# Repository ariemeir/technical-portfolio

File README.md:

# Technical Portfolio — Arie Meir

Representative projects, published for reference.

**→ [Browse all source on GitHub](https://github.com/ariemeir/technical-portfolio)**

## Projects

### [RoboImplant](roboimplant/) — non-invasive spinal implant adjustment system

A motorized orthopedic implant that lengthens a spinal distraction rod without
surgery, for treating early-onset scoliosis in growing children. Full-stack
across four disciplines:

- **Embedded** — AVR C firmware on an ATmega1284P: real-time motor control via a
  DS1267 digital pot into a maxon ESCON servo controller, interrupt-driven
  rotation counting, and current-threshold coupling detection as the primary
  safety interlock.
- **Mobile** — Android clinician console over Bluetooth SPP, with a custom
  line-oriented ASCII protocol, live telemetry, 3D visualization, and patient
  records.
- **Electronics** — EAGLE schematic and board layout for the controller,
  including the analog current/voltage sensing chain.
- **Mechanical** — SolidWorks enclosure for the handheld driver unit.

<p align="center">
  
  <br>
  <em>The handheld driver unit (v1)</em>
</p>

**→ [Read the one-page case study (PDF)](roboimplant/docs/roboimplant-case-study-arie-meir.pdf)**

Research prototype, ~2012–2013. Not a cleared medical device.
See [`roboimplant/NOTICE.md`](roboimplant/NOTICE.md) for rights and third-party
attribution.

---

### [3D Scanner](3dscanner/) — turntable photogrammetry rig

A DIY tabletop 3D scanner built to solve a real fabrication problem: an artist needed
larger and deeper variants of a commercially molded clay flower that existed only as a
physical object. It takes that object and produces a printable, watertight STL. Five
subsystems bound together by explicit contracts:

- **iOS** — **ScannerCam**, an iPhone camera server with a hand-rolled HTTP/1.1
  stack on `NWListener`: 13 REST routes, bearer auth with constant-time comparison,
  Keychain token storage, and hard locks on focus, exposure, and white balance.
  SwiftUI + AVFoundation, zero third-party packages.
- **Orchestration** — a Python session controller driving the scan loop across two
  machines, with idempotent retries, resumable sessions, and a five-stage SHA-256
  integrity chain from the phone's memory to the final archive.
- **Embedded** — an Arduino that controls the turntable by *impersonating its
  infrared remote*, replaying NEC codes reverse-engineered with a majority-vote
  capture sketch. No data port, no feedback, no encoder.
- **Reconstruction** — a Swift CLI over Apple Object Capture (RealityKit), chosen
  after COLMAP was tested and rejected for being CUDA-only on Apple Silicon.
- **Print prep** — a PyMeshLab pass that makes the mesh watertight, orients it by
  PCA, and scales it to real millimetres for printing and silicone-mold casting.

<p align="center">
  
  <br>
  <em>Input and output: the original ceramic dish, and a printed reproduction
  scanned from it.</em>
</p>

```
object ─→ 72 photos ─→ pose solve ─→ textured mesh ─→ watertight STL ─→ printed master
          locked        Object          USDZ/OBJ        PyMeshLab         silicone mold
          optics        Capture                         repair            → cast copies
```

The engineering centrepiece is control of an actuator that cannot be observed: the
turntable answers only to a fire-and-forget infrared *toggle*, so the controller
tracks an explicit assumed state and halts for human realignment on any ambiguity
rather than guessing and silently desynchronising the scan.

**→ [Read the one-page case study (PDF)](3dscanner/docs/3dscanner-case-study-arie-meir.pdf)**
· [Engineering log](3dscanner/docs/engineering-log.md)
· [Technical spec](3dscanner/docs/scannercam_spec.md)

Personal project, 2026. Working single-operator rig at late-prototype maturity.
See [`3dscanner/NOTICE.md`](3dscanner/NOTICE.md) for rights and attribution.

---

### [WifeSignal](wifesignal/) — a traffic light for the office door

A three-colour desk lamp that lets one person in the house tell another *how much
this can wait*. The office is a separate building: music on, windows closed, phone
face-down and unchecked for hours — which is the point, and which makes it a sealed
box. Text-and-hope fails when it matters; walking over always costs an interruption
whether or not the thing was urgent. The missing piece was never notification, it
was **priority expressed before the interruption happens**. Five components across
four disciplines:

- **iOS** — a SwiftUI app in 333 lines with no third-party packages and no
  Bluetooth: three priority buttons, a 5 s status poll, and a *Waiting… → Seen ♥*
  acknowledgement card that closes the loop for the sender.
- **Server** — a 290-line aiohttp + bleak bridge on a Mac, sharing one asyncio event
  loop, that exists because an iPhone cannot reliably be a BLE central for a device
  in another building. Bearer auth with constant-time comparison, exposed to a
  Tailscale tailnet only.
- **Embedded** — ESP32-C3 firmware over NimBLE exposing one service, one
  characteristic, one byte, with physical button presses as the acknowledgement path.
- **Electronics** — a custom two-layer KiCad board: three low-side lamp drivers,
  entirely through-hole, shaped and notched to match the enclosure.
- **Mechanical** — a 440-line Fusion 360 *script* that generates the two-part
  enclosure from derived dimensions, versioned in-band and guarded step by step.

<p align="center">
  
  <br>
  <em>Green — <strong>whenever you're free</strong>. The speaker beside it is the
  reason the project exists.</em>
</p>

```
tap ─→ HTTPS ─→ aiohttp ─→ 1 byte ─→ ESP32-C3 ─→ lamp ─→ physical ─→ "Seen ♥"
       tailnet   desired    over BLE   NimBLE              press       on her
       only      state                                     = ack       phone
```

The engineering centrepiece is the return path. Because the state characteristic is
bidirectional, three different events — the server's own write echoed back, a human
pressing the button, and a device that has drifted — all arrive as an identical
one-byte notification. They are separated with no timers, correlation IDs, or
sequence numbers: every notify is simply compared against the state the server
already intends, which collapses the whole problem into three branches and makes
recovery after a reboot or a reflash automatic.

**→ [Read the one-page case study (PDF)](wifesignal/docs/wifesignal-case-study-arie-meir.pdf)**
· [Full case study](wifesignal/) · [Server](wifesignal/server/) · [iOS app](wifesignal/app/)
· [Firmware](wifesignal/firmware/) · [Hardware](wifesignal/device/)

Personal project, 2026. In daily use.
See [`wifesignal/NOTICE.md`](wifesignal/NOTICE.md) for rights and attribution.

---

Each project directory carries its own README and rights notice. Unless stated
otherwise in a project's `NOTICE.md`, this work is published for reference only
and is not offered under an open-source license.

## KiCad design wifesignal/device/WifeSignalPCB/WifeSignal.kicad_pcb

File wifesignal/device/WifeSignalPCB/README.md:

# KiCad Project

Schematic, layout and fabrication output for the lamp-driver board.

**→ [Browse this directory on GitHub](https://github.com/ariemeir/technical-portfolio/tree/main/wifesignal/device/WifeSignalPCB)**

## Which files matter

| File set | Status |
|---|---|
| `WifeSignal3ch.*` | **The board that was fabricated.** 3 channels, routed (62 track segments), outlined, gerbers exported. |
| `WifeSignal.*` | **Design history.** A stripped 1-channel variant saved minutes apart from the 3-channel schematic during exploration. Never routed, no board outline, never made. |
| `output/` | Gerbers, drill files and the job file sent for fabrication (KiCad 10.0.4). |
| `ERC.json` | Electrical rules check output. |

Only `WifeSignal3ch` exists physically. The 1-channel variant is kept because it
shows the design being narrowed before it was widened — the project briefly
considered proving one channel in copper before committing to three, and decided the
protoboard prototype had already answered that question.

## Board summary

| | |
|---|---|
| Size | 41.0 × 88.5 mm |
| Layers | 2 (F.Cu / B.Cu), 2 copper zones |
| Vias | none |
| Technology | entirely through-hole |
| Drill tools | 0.75 / 0.80 / 1.00 mm; **no** non-plated holes |
| Outline | flat one end, R20.5 arc the other, four R4.7 C-notches at (±16, ±18.5) mm |

## Reading the schematic

The design is three identical low-side switches. Rather than rely on the reader to
infer it, the schematic carries its own notes in the drawing:

```
Each channel identical: GPIO ->1k-> S8050 base; emitter->GND; collector-> button LED-.
Button conn (J3/J4/J5): pin1 LED+ ->+5V, pin2 LED- ->collector, pin3 COM ->GND, pin4 NO ->switch GPIO.
RED CHANNEL     lamp GPIO6  / switch GPIO3
YELLOW CHANNEL  lamp GPIO7  / switch GPIO4
GREEN CHANNEL   lamp GPIO10 / switch GPIO5
Refs R1/Q1/J3=RED  R2/Q2/J4=YELLOW  R3/Q3/J5=GREEN  (carry to PCB silkscreen).
```

That last line is the useful habit: the reference-designator-to-channel mapping is
written into the drawing *and* onto the silkscreen, so the board can be assembled
and debugged without the schematic open.

## ⚠️ Q1–Q3 are wrong on this schematic

The drawing specifies **S8050 NPN**. The board was populated with **S8550 PNP** from
an assortment kit, which inverts the drive logic (GPIO LOW = lamp on). The firmware
is written against the parts that are actually soldered.

This has deliberately not been corrected, and the discrepancy is documented here, in
[`device/README.md`](../README.md), and in the firmware header. If the board is ever
re-spun, this is the first thing to fix — and the firmware's `applyLamps()` must be
inverted in the same commit.

## Regenerating the fabrication output

`output/` is generated from `WifeSignal3ch.kicad_pcb` and is committed only so the
board that was actually ordered is recoverable. Re-export from KiCad's plot dialog
rather than editing anything in it by hand.

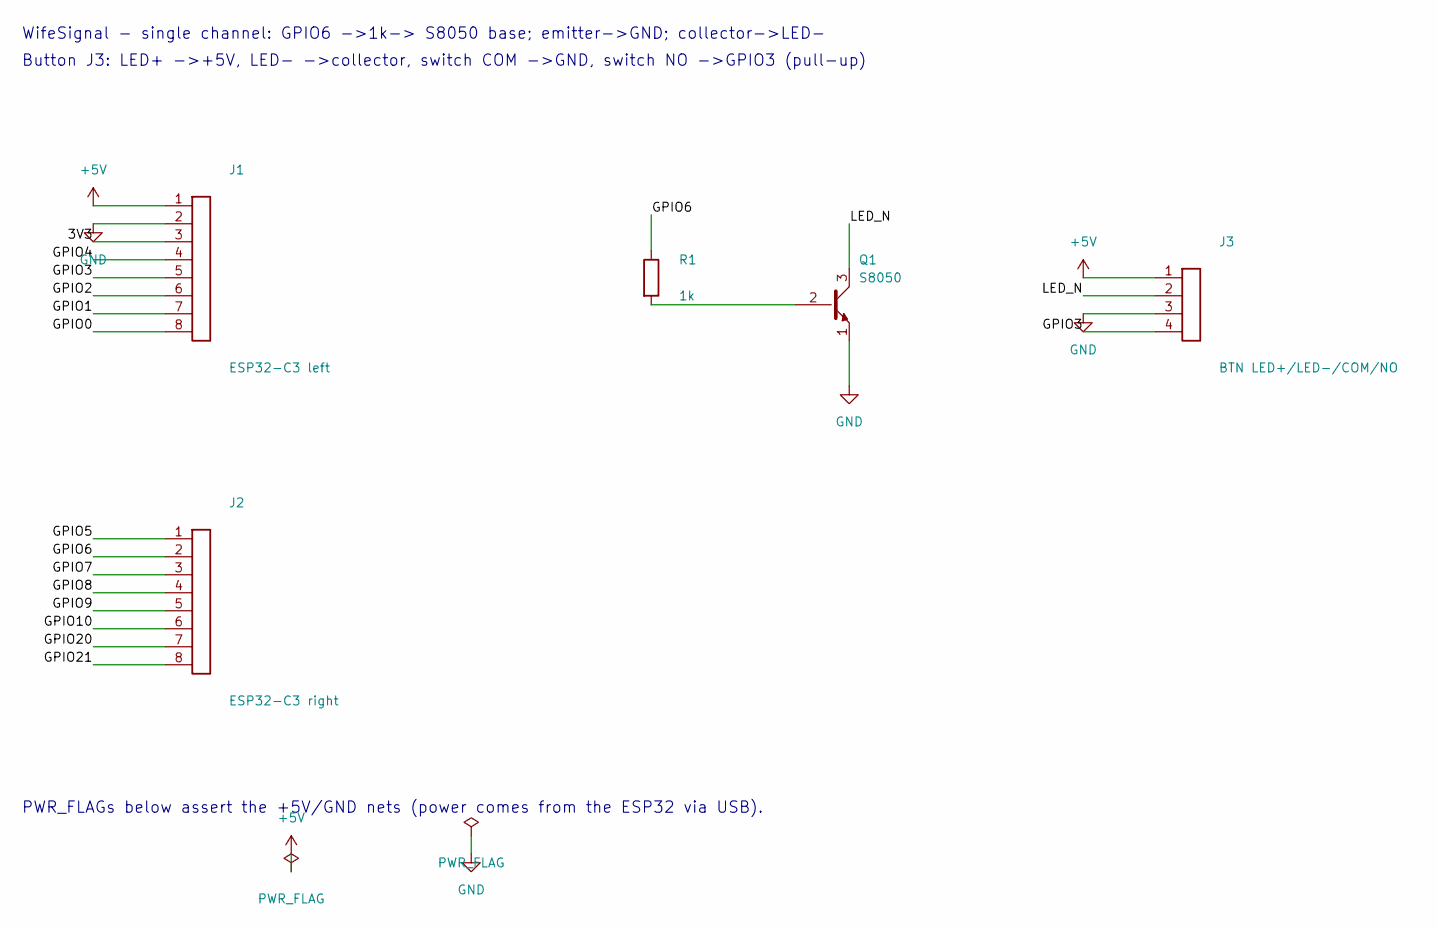
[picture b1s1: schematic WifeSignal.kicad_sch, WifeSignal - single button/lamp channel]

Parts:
J1: ESP32-C3 left; PinHeader_1x08_P2.54mm_Vertical
J2: ESP32-C3 right; PinHeader_1x08_P2.54mm_Vertical
J3: BTN LED+/LED-/COM/NO; PinHeader_1x04_P2.54mm_Vertical
Q1: S8050; TO-92_Inline
R1: 1k; R_Axial_DIN0207_L6.3mm_D2.5mm_P7.62mm_Horizontal

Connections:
+5V: J1.1, J3.1
/3V3: J1.3
/GPIO0: J1.8
/GPIO1: J1.7
/GPIO2: J1.6
/GPIO3: J1.5, J3.4
/GPIO4: J1.4
/GPIO5: J2.1
/GPIO6: J2.2, R1.1
/GPIO7: J2.3
/GPIO8: J2.4
/GPIO9: J2.5
/GPIO10: J2.6
/GPIO20: J2.7
/GPIO21: J2.8
/LED_N: J3.2, Q1.3 (C)
GND: J1.2, J3.3, Q1.1 (E)
unnamed: Q1.2 (B), R1.2

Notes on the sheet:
WifeSignal - single channel: GPIO6 ->1k-> S8050 base; emitter->GND; collector->LED-
PWR_FLAGs below assert the +5V/GND nets (power comes from the ESP32 via USB).
Button J3: LED+ ->+5V, LED- ->collector, switch COM ->GND, switch NO ->GPIO3 (pull-up)

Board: 2 copper layers, 5 parts (0 on the bottom side), 6 nets, no tracks yet.

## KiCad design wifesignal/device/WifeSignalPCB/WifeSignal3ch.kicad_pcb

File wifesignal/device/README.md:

# Device — PCB and Enclosure

The physical object: a custom two-layer PCB carrying three lamp-driver channels, an
ESP32-C3 on removable headers, and three 30 mm illuminated arcade buttons in a
3D-printed two-part enclosure.

**→ [Browse this directory on GitHub](https://github.com/ariemeir/technical-portfolio/tree/main/wifesignal/device)**

| | |
|:--:|:--:|
|  |  |
| **Rev A, as fabricated.** Entirely through-hole, two layers, 62 track segments, no vias. The rounded end and the four edge notches are dictated by the enclosure. | **Mechanical fit.** The board drops over four M4 pillars. The notch centres at (±16, ±18.5) mm are cut to clear them exactly. |

## The circuit

Three identical channels, each a textbook low-side switch:

```
GPIO ──[1k]── base ; emitter ── GND ; collector ── lamp cathode
                                      lamp anode ── +5V
```

| Ref | Part | Notes |
|---|---|---|
| J1, J2 | 1×8 pin headers | ESP32-C3 SuperMini Plus, on **female** headers so the module is removable |
| J3, J4, J5 | 1×4 pin headers | One per button: `LED+`, `LED−`, switch `COM`, switch `NO` |
| Q1, Q2, Q3 | S8050 NPN *on the schematic* | **S8550 PNP as actually soldered** — see below |
| R1, R2, R3 | 1 kΩ | Base resistors |

Channel mapping carries through to the silkscreen: `R1/Q1/J3` = red, `R2/Q2/J4` =
yellow, `R3/Q3/J5` = green. Power arrives from the ESP32's USB connector, so three
`PWR_FLAG`s assert the +5 V and GND nets for the electrical rules check.

## ⚠️ The schematic is knowingly wrong

The board was populated with **S8550 PNP** transistors from an assortment kit; the
schematic specifies **S8050 NPN**. The part numbers differ by one character. This
was discovered only when the lamps behaved backwards.

A PNP low-side driver inverts the control sense — **GPIO LOW turns the lamp on** —
and the fix lives in the firmware rather than in a rework, because reworking three
transistors on an otherwise working board buys nothing but agreement with a drawing.
The schematic is left as-is and documented as wrong in three places, including a
shouted comment in the firmware header telling the next engineer not to "fix" it.

## Board geometry

41.0 × 88.5 mm. Flat at one end, a R20.5 semicircular arc at the other. Four
C-shaped notches (R4.7) centred at (±16, ±18.5) mm from the board centre.

The notches are the interesting part: the electrical and mechanical designs are
**dimensionally coupled**, and both say so in comments. The enclosure generator
places its four M4 pillars at exactly those coordinates, and the board is cut to
drop over them. Change one and the other stops fitting.

## Directories

| Path | Contents |
|---|---|
| [`WifeSignalPCB/`](WifeSignalPCB/) | KiCad project. `WifeSignal3ch.*` is the board that was fabricated; `WifeSignal.*` is an unrouted 1-channel variant kept as design history. `output/` holds the gerbers and drill files sent for fabrication. |
| [`enclosure/`](enclosure/) | The Fusion 360 script that generates the enclosure — the CAD source of truth. |

## Bill of materials

| Qty | Item |
|---|---|
| 1 | ESP32-C3 SuperMini Plus |
| 3 | 30 mm illuminated arcade buttons (red, yellow, green), 4-terminal |
| 3 | S8550 PNP transistors, TO-92 |
| 3 | 1 kΩ resistors, axial |
| 2 | 1×8 female pin headers |
| 3 | 1×4 pin headers |
| 4 | M4 × 10 bolts + nuts (press-fit into the printed pillars) |
| 1 | Custom PCB, 41.0 × 88.5 mm, two layers, through-hole |

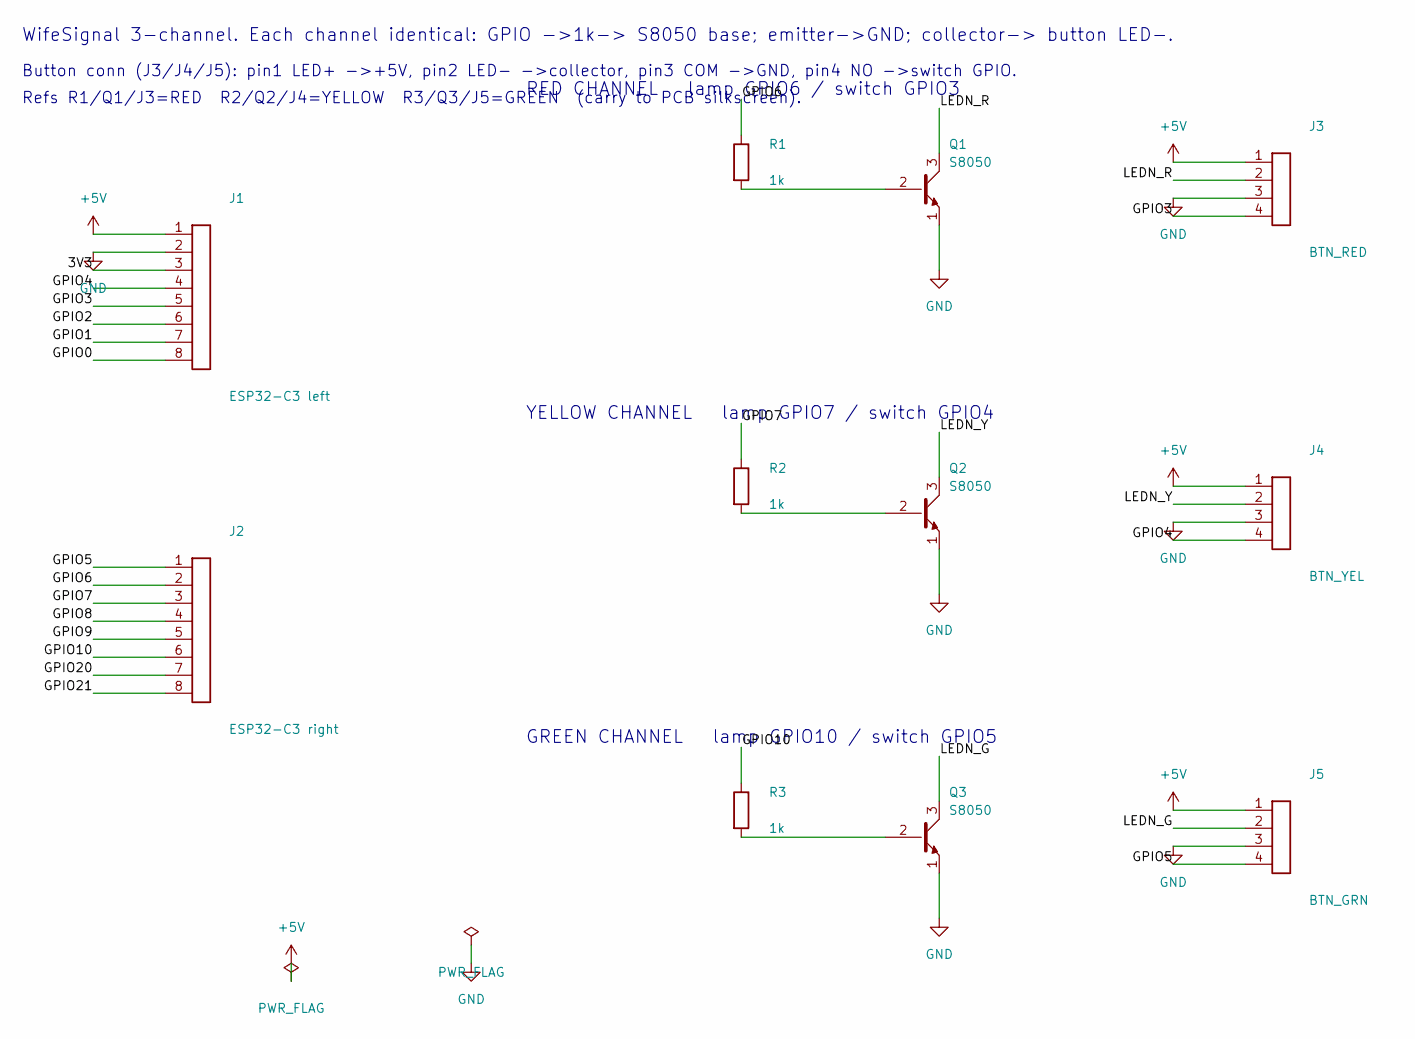
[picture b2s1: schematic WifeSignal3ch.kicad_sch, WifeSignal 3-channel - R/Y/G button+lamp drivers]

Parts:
J1: ESP32-C3 left; PinHeader_1x08_P2.54mm_Vertical
J2: ESP32-C3 right; PinHeader_1x08_P2.54mm_Vertical
J3: BTN_RED; PinHeader_1x04_P2.54mm_Vertical
J4: BTN_YEL; PinHeader_1x04_P2.54mm_Vertical
J5: BTN_GRN; PinHeader_1x04_P2.54mm_Vertical
Q1, Q2, Q3: S8050; TO-92_Inline
R1, R2, R3: 1k; R_Axial_DIN0207_L6.3mm_D2.5mm_P7.62mm_Horizontal

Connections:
+5V: J1.1, J3.1, J4.1, J5.1
/3V3: J1.3
/GPIO0: J1.8
/GPIO1: J1.7
/GPIO2: J1.6
/GPIO3: J1.5, J3.4
/GPIO4: J1.4, J4.4
/GPIO5: J2.1, J5.4
/GPIO6: J2.2, R1.1
/GPIO7: J2.3, R2.1
/GPIO8: J2.4
/GPIO9: J2.5
/GPIO10: J2.6, R3.1
/GPIO20: J2.7
/GPIO21: J2.8
/LEDN_G: J5.2, Q3.3 (C)
/LEDN_R: J3.2, Q1.3 (C)
/LEDN_Y: J4.2, Q2.3 (C)
GND: J1.2, J3.3, J4.3, J5.3, Q1.1 (E), Q2.1 (E), Q3.1 (E)
unnamed: Q1.2 (B), R1.2
unnamed: Q2.2 (B), R2.2
unnamed: Q3.2 (B), R3.2

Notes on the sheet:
GREEN CHANNEL lamp GPIO10 / switch GPIO5
RED CHANNEL lamp GPIO6 / switch GPIO3
Button conn (J3/J4/J5): pin1 LED+ ->+5V, pin2 LED- ->collector, pin3 COM ->GND, pin4 NO ->switch GPIO.
YELLOW CHANNEL lamp GPIO7 / switch GPIO4
Refs R1/Q1/J3=RED R2/Q2/J4=YELLOW R3/Q3/J5=GREEN (carry to PCB silkscreen).
WifeSignal 3-channel. Each channel identical: GPIO ->1k-> S8050 base; emitter->GND; collector-> button LED-.

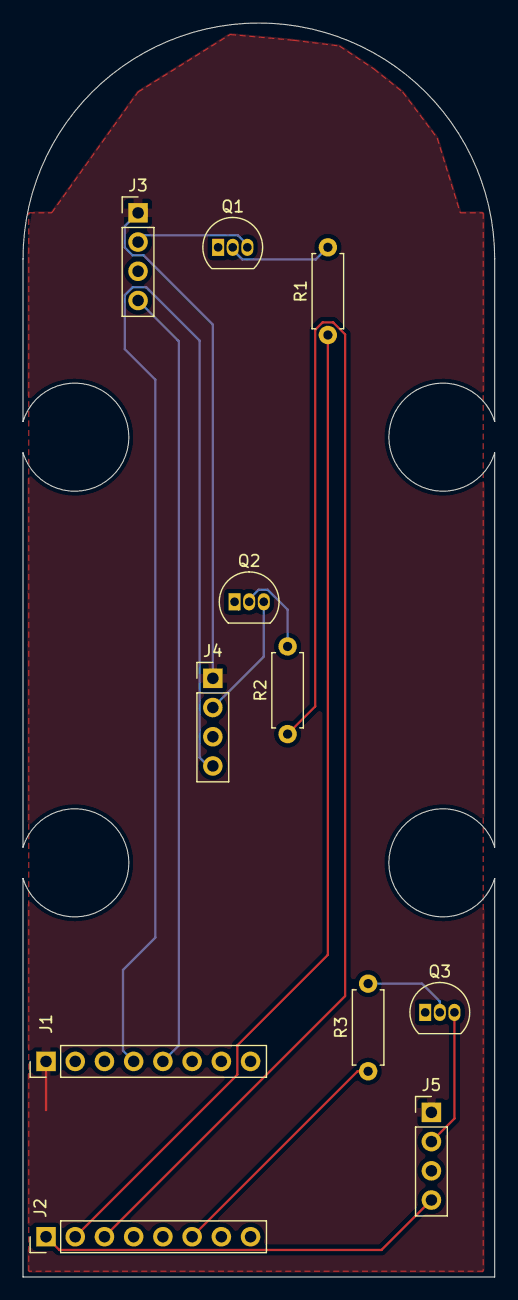
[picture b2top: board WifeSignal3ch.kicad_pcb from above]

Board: 2 copper layers, 41.0 x 109.0 mm, 11 parts (0 on the bottom side), 14 nets.

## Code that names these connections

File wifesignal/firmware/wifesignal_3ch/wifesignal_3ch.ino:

/*
 * WifeSignal - 3-channel BLE firmware (Rev A PCB)
 * Board:  ESP32-C3 SuperMini Plus (ESP32C3 Dev Module, USB CDC On Boot = Enabled)
 * BLE:    NimBLE-Arduino v2.x
 *
 * One STATE byte drives three illuminated arcade buttons:
 *   0 = all off, 1 = red, 2 = yellow, 3 = green  (single active light)
 *
 * Pins (as built):
 *   switches  RED=GPIO3  YEL=GPIO4  GRN=GPIO5   (INPUT_PULLUP, press = LOW, COM -> GND)
 *   lamps     RED=GPIO6  YEL=GPIO7  GRN=GPIO10
 *   onboard LED GPIO8 (INVERTED, LOW = ON) mirrors state != 0
 *
 * LAMP POLARITY: drivers are S8550 PNP (not the S8050 NPN on the schematic -
 * assortment-kit mixup, the soldered parts win). GPIO LOW = lamp ON,
 * HIGH = lamp OFF. Do not "fix" this to NPN logic.
 *
 * Button semantics (must match server.py's echo-suppression logic):
 *   press any button while state != 0 -> state = 0 (physical acknowledge)
 *   press a button while state == 0   -> state = that button's color
 *     (the server writes it back to 0; reserved "ping back" hook)
 * A BLE central can WRITE (0-3), READ, and gets NOTIFY on every change.
 */

#include <NimBLEDevice.h>

#define SVC_UUID   "6d5f0001-4b6b-4a3a-9e1e-2a7b1c9f0001"
#define STATE_UUID "6d5f0002-4b6b-4a3a-9e1e-2a7b1c9f0002"

const int NCH = 3;
const int BTN[NCH]  = {3, 4, 5};    // red, yellow, green
const int LAMP[NCH] = {6, 7, 10};   // red, yellow, green (LOW = ON, PNP)
const int LEDB = 8;                 // onboard LED, INVERTED (LOW = ON)

NimBLECharacteristic* stateChar = nullptr;
uint8_t state = 0;                  // 0=off, 1=red, 2=yellow, 3=green
bool connected = false;

// debounce, per button
int lastRead[NCH] = {HIGH, HIGH, HIGH};
uint32_t lastEdge[NCH] = {0, 0, 0};
bool handled[NCH] = {false, false, false};

void applyLamps() {
  for (int i = 0; i < NCH; i++)
    digitalWrite(LAMP[i], (state == i + 1) ? LOW : HIGH);   // PNP: LOW = ON
  digitalWrite(LEDB, state ? LOW : HIGH);                   // onboard: inverted
}

void pushState(bool doNotify) {
  stateChar->setValue(&state, 1);
  if (doNotify && connected) stateChar->notify();
}

class StateCallbacks : public NimBLECharacteristicCallbacks {
  void onWrite(NimBLECharacteristic* c, NimBLEConnInfo& info) override {
    std::string v = c->getValue();
    if (v.empty()) return;
    state = (v[0] <= 3) ? v[0] : 0;
    applyLamps();
    pushState(true);
    Serial.printf("write -> state %d\n", state);
  }
};

class ServerCallbacks : public NimBLEServerCallbacks {
  void onConnect(NimBLEServer* s, NimBLEConnInfo& i) override {
    connected = true; Serial.println("central connected");
  }
  void onDisconnect(NimBLEServer* s, NimBLEConnInfo& i, int reason) override {
    connected = false; Serial.println("central disconnected");
    NimBLEDevice::startAdvertising();
  }
};

void setup() {
  // Lamps OFF (HIGH) before anything else - latch the level, then enable output
  for (int i = 0; i < NCH; i++) {
    digitalWrite(LAMP[i], HIGH);
    pinMode(LAMP[i], OUTPUT);
    digitalWrite(LAMP[i], HIGH);
  }
  digitalWrite(LEDB, HIGH);
  pinMode(LEDB, OUTPUT);
  digitalWrite(LEDB, HIGH);
  for (int i = 0; i < NCH; i++) pinMode(BTN[i], INPUT_PULLUP);

  Serial.begin(115200);
  applyLamps();

  Serial.printf("pins -> BTN=%d/%d/%d  LAMP=%d/%d/%d (R/Y/G)  LEDB=%d\n",
                BTN[0], BTN[1], BTN[2], LAMP[0], LAMP[1], LAMP[2], LEDB);

  NimBLEDevice::init("WifeSignal");
  NimBLEDevice::setPower(ESP_PWR_LVL_P9);

  NimBLEServer* server = NimBLEDevice::createServer();
  server->setCallbacks(new ServerCallbacks());

  NimBLEService* svc = server->createService(SVC_UUID);
  stateChar = svc->createCharacteristic(STATE_UUID,
      NIMBLE_PROPERTY::READ | NIMBLE_PROPERTY::WRITE | NIMBLE_PROPERTY::NOTIFY);
  stateChar->setCallbacks(new StateCallbacks());
  pushState(false);
  svc->start();

  NimBLEAdvertising* adv = NimBLEDevice::getAdvertising();
  adv->addServiceUUID(SVC_UUID);
  adv->setMinInterval(160);   // 100 ms
  adv->setMaxInterval(320);   // 200 ms
  adv->setName("WifeSignal");
  adv->start();
  Serial.println("BLE up - advertising as WifeSignal");
}

void loop() {
  uint32_t now = millis();
  for (int i = 0; i < NCH; i++) {
    int r = digitalRead(BTN[i]);
    if (r != lastRead[i]) { lastRead[i] = r; lastEdge[i] = now; }
    if (now - lastEdge[i] > 40) {
      if (r == LOW && !handled[i]) {
        handled[i] = true;
        state = state ? 0 : (uint8_t)(i + 1);
        applyLamps();
        pushState(true);
        Serial.printf("press btn %d -> state %d\n", i + 1, state);
      } else if (r == HIGH) {
        handled[i] = false;
      }
    }
  }
  delay(5);
}
